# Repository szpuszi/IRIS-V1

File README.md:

# IRIS (Infra-Red Interrupt System)
IRIS is an open-hardware project designed to teach the basics of electronics, soldering and basic components. With this device you can shut down almost any IR-controlled device, like TVs.

The firmware is currently in **ALPHA** stage, it does not fully work now. It will be updated when I get the parts.
## Why I made it?
I created IRIS for people interested in hardware hacking. It help young enthusiasts understand how different components communicate. By soldering the PCB themselves, makers see the connections between the code and the physical hardware.

## How it works? 
1. Brain: The ATtiny85 microcontroller stores the IR codes.
2. Logic: When the button is pressed the MCU wakes up and sends a modulated signal.
3. Driver: Since IR LEDs require more current than the MCU can provide, we use a IRLZ44N MOSFET.
4. Output: Two TSAL6100 IR diodes transmit the signal.

## Power
IRIS uses LP403035.
The battery is charged using PiMoroni PIM611.

## What will you learn?
- Basic Components: Understanding why we use resistors, electrolytic and ceramic capacitors and how they work.
- Soldering: Working with THT and SMD components. Cold joints etc.
- Transistor Logic: Understanding how a MOSFET uses a tiny voltage to control a much larger current flow.
- Power Management: Learning to work with Li-Po batteries safely, including charging.
- Programming: How to turn an Arduino into an ISP programmer to flash firmware onto standalone microcontrollers like the ATtiny85.
- Microcontroller Basics: Getting to know ATtiny85, compact and universal microcontroller. How the ATtiny85 manages "deep sleep" mode to save battery (almost no use) and wakes up with instantly on a button press. 
- Reading Schematics: Learn how to understand schematics. Turning a digital circuit design into a working device.
- Ethical Hacking: What you can, and what you shouldn't do.
- Ordering your PCB: Learn how to order your PCB.

## BOM
BOM is located [Here](Manufacturing/BOM.csv)

Total is ≈ 60USD

You will also need:
- soldering iron and solder
- glue (for the case)
- double sided tape (for battery, pcb and charging module)
- cutting pliers

## Guide
The educational manual and Troubleshooting FAQ are currently being written.

<sub>The full assembly guide is planned and will begin development as soon as the parts arrive.</sub>

## Fallout Zine Page

# Gallery  
## PCB

## Schematic

## 3D PCB

## Case

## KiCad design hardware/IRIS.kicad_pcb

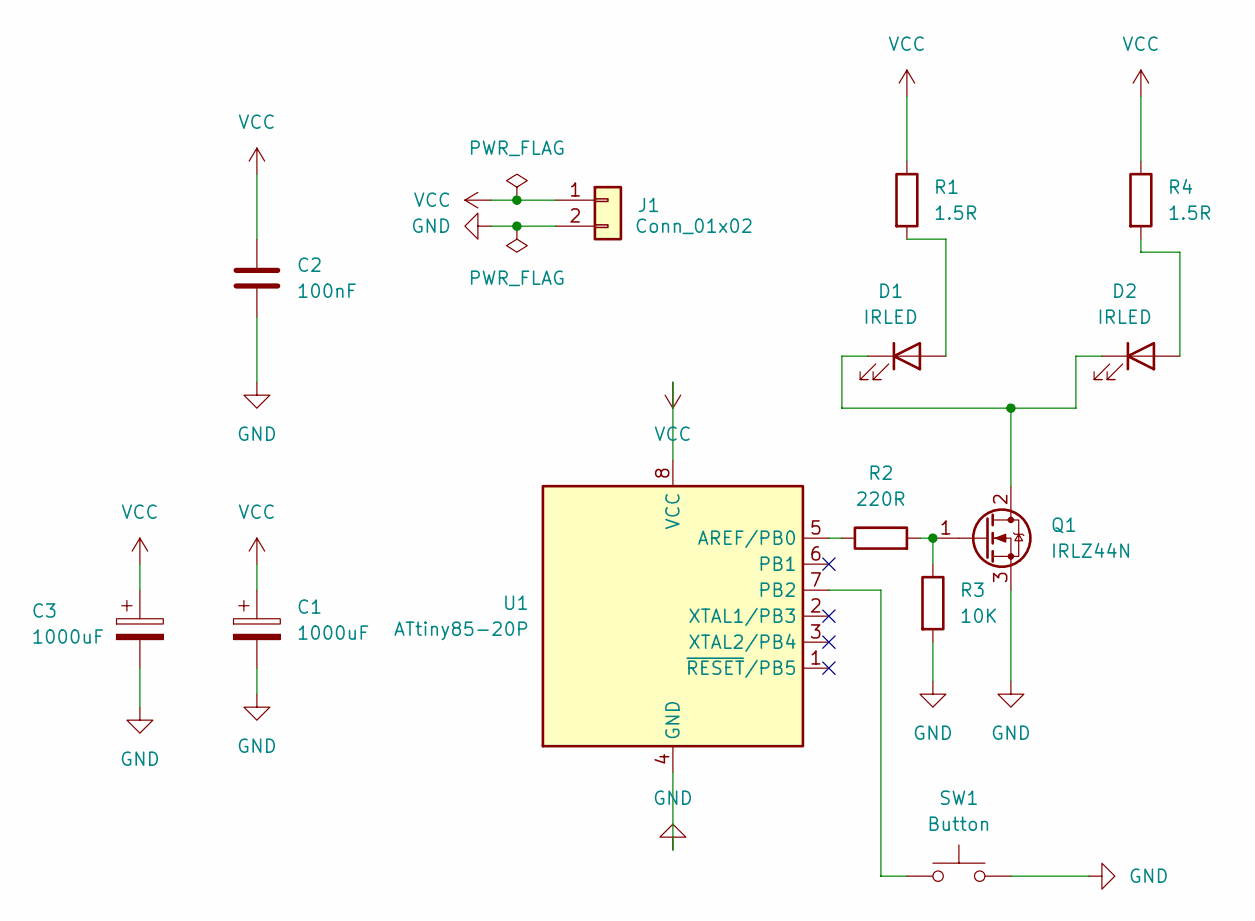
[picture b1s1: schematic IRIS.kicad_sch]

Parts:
C1, C3: 1000uF; CP_Radial_D8.0mm_P3.50mm
C2: 100nF; C_Disc_D4.3mm_W1.9mm_P5.00mm
D1, D2: IRLED; LED_D5.0mm
J1: Conn_01x02; PinHeader_1x02_P2.54mm_Vertical
Q1: IRLZ44N; TO-220-3_Vertical
R1, R4: 1.5R; R_2512_6332Metric
R2: 220R; R_Axial_DIN0207_L6.3mm_D2.5mm_P7.62mm_Horizontal
R3: 10K; R_Axial_DIN0207_L6.3mm_D2.5mm_P7.62mm_Horizontal
SW1: Button; SW_PUSH_6mm
U1: ATtiny85-20P; DIP-8_W7.62mm

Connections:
GND: C1.2, C2.2, C3.2, J1.2 (GND), Q1.3 (S), R3.2, SW1.2, U1.4 (GND)
unnamed: D1.2 (A), R1.2
unnamed: D1.1 (K), D2.1 (K), Q1.2 (D)
unnamed: D2.2 (A), R4.2
unnamed: Q1.1 (G), R2.2, R3.1
unnamed: R2.1, U1.5 (AREF/PB0)
unnamed: SW1.1, U1.7 (PB2)
VCC: C1.1, C2.1, C3.1, J1.1 (BAT), R1.1, R4.1, U1.8 (VCC)

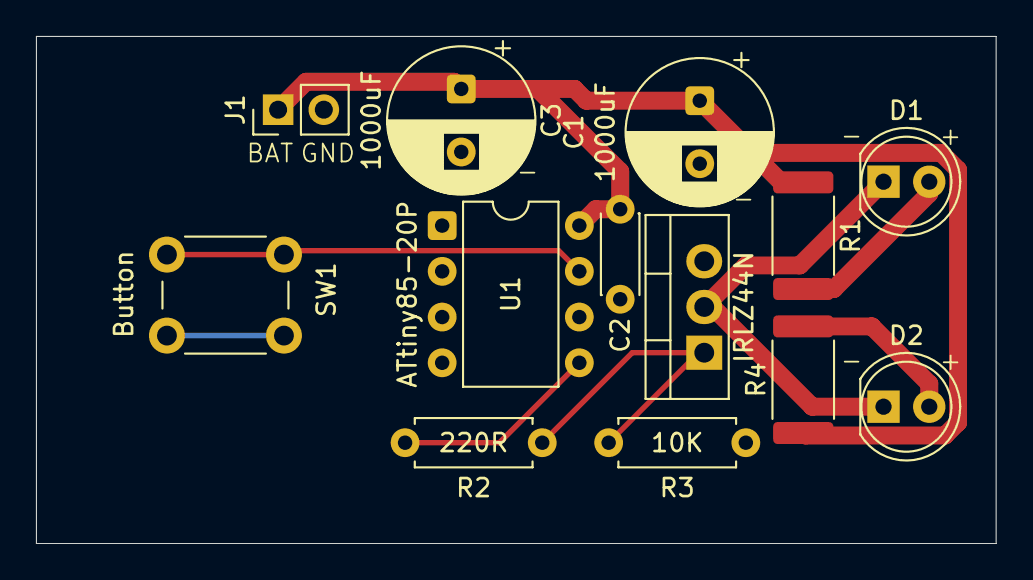
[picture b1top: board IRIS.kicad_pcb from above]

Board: 2 copper layers, 53.3 x 28.2 mm, 13 parts (0 on the bottom side), 8 nets.

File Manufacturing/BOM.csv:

Reference,Qty,Value,Description,Link
"C1,C3",2,1000uF,Electrolytic capacitor,https://www.tme.eu/pl/details/eeufr1c102l/kondensatory-elekt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
C2,1,100nF,Ceramic capacitor,https://www.tme.eu/pl/details/k104k10x7rf5uh5/kondensatory-c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
"D1,D2",2,IRLED,TSAL6100,https://www.tme.eu/pl/details/tsal6100/diody-led-ir/vishay/
J1,1,Conn_01x02,28AWG wire for connecting battery and PCB,https://allegro.pl/oferta/przewod-awg28-14-zylowy-wielokolor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
Q1,1,IRLZ44N,IRLZ44N TO-220,https://www.tme.eu/pl/details/irlz44npbf/tranzystory-z-kanal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
"R1,R4",2,1.5R,1.5Ω 3W Resistor,https://www.tme.eu/pl/details/sp123wf150kt2e/rezystory-smd/r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
R2,1,220R,220Ω Resistor,https://www.tme.eu/pl/details/1_4w220r/rezystory-tht/royaloh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
R3,1,10K,10KΩ Resistor,https://www.tme.eu/pl/details/cf1_4w-10k/rezystory-tht/sr-passives/
SW1,1,Button,Tact switch 6x6mm 17mm,https://www.tme.eu/pl/details/tl1105lf250q/mikroprzelaczniki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
U1,1,ATtiny85-20P,ATtiny85-20PU (DIP-8),https://www.tme.eu/pl/details/attiny85-20pu/rodzina-avr-8-bi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
none,1,none,Breadboard (for programming ATtiny85-20P),https://botland.com.pl/plytki-stykowe/19943-plytka-stykowa-j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
none,1,none,"Arduino Nano, or any other arduino clone (used for programming ATtiny85-20P)",https://allegro.pl/oferta/nano-3-0-atmega328-ch340-kompatybi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
none,1,none,Dupont wires (for connecting Arduino with ATtiny85-20P and breadboard),https://botland.com.pl/przewody-polaczeniowe-mesko-meskie/19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
none,1,none,Li-Pol charger PiMoroni PIM611,https://botland.com.pl/moduly-ladowania-lipol-usb-micro-usb/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
none,1,none,LP403035 Li-Po,https://www.tme.eu/pl/details/aky-lp403035/akumulatory/akyga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
none,1,none,2-pin JST plug,https://botland.com.pl/przewody-i-zlacza-zasilajace/6563-wty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
none,1,none,heat-shrink tubing,https://botland.com.pl/rurki-termokurczliwe/5374-zestaw-rure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
TOTAL,≈ 60USD, , ,

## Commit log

2026-04-19 Add MIT License to the project
2026-04-21 Rename IRIS.csv to Manufacturing/BOM.csv
2026-04-21 Update BOM with new components and links
    Added new components including Adafruit Micro-Lipo Charger and updated existing entries.
2026-04-21 Update BOM with new components and links
    Added new components and updated existing entries in the BOM.
2026-04-21 Rename IRIS.png to images/zine.png
2026-04-21 Rename zine.png to zine_page.png
2026-04-21 Rename zine_page.png to zine_.png
2026-04-21 Rename IRIS.png to zine_page.png
2026-04-21 Rename zine_page.png to images/zine_page.png
2026-04-21 Create gvh
2026-04-21 Add PCB image to README gallery section
2026-04-21 Create i
2026-04-21 Rename 3d_models/i to 3d_models/case/i
2026-04-21 Update README with expanded learning topics and guide section
    Expanded the learning section to include various topics such as soldering, transistor logic, and programming with Arduino. Added a guide section indicating ongoing development of educational material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
2026-04-24 Clarify capacitor types in README
    Updated capacitor types in the learning section.
2026-04-24 Update README.md with additional images
    Added new images to the Gallery section for PCB, Schematic, and 3D PCB.
2026-04-25 Revise BOM with new components and pricing
    Updated the BOM with new components and links.
2026-04-25 Revise BOM with new component specifications
    Updated component values and links in BOM.
2026-04-25 Update BOM.csv with new component links and details
2026-04-30 Rename 3d_models/IRIS_CASE_BOTTOM(2).stl to 3d_models/3d_printing/IRIS_CASE_BOTTOM.stl
2026-04-30 Rename 3d_models/IRIS_CASE_TOP(2).stl to 3d_models/3d_printing/IRIS_CASE_TOP.stl
